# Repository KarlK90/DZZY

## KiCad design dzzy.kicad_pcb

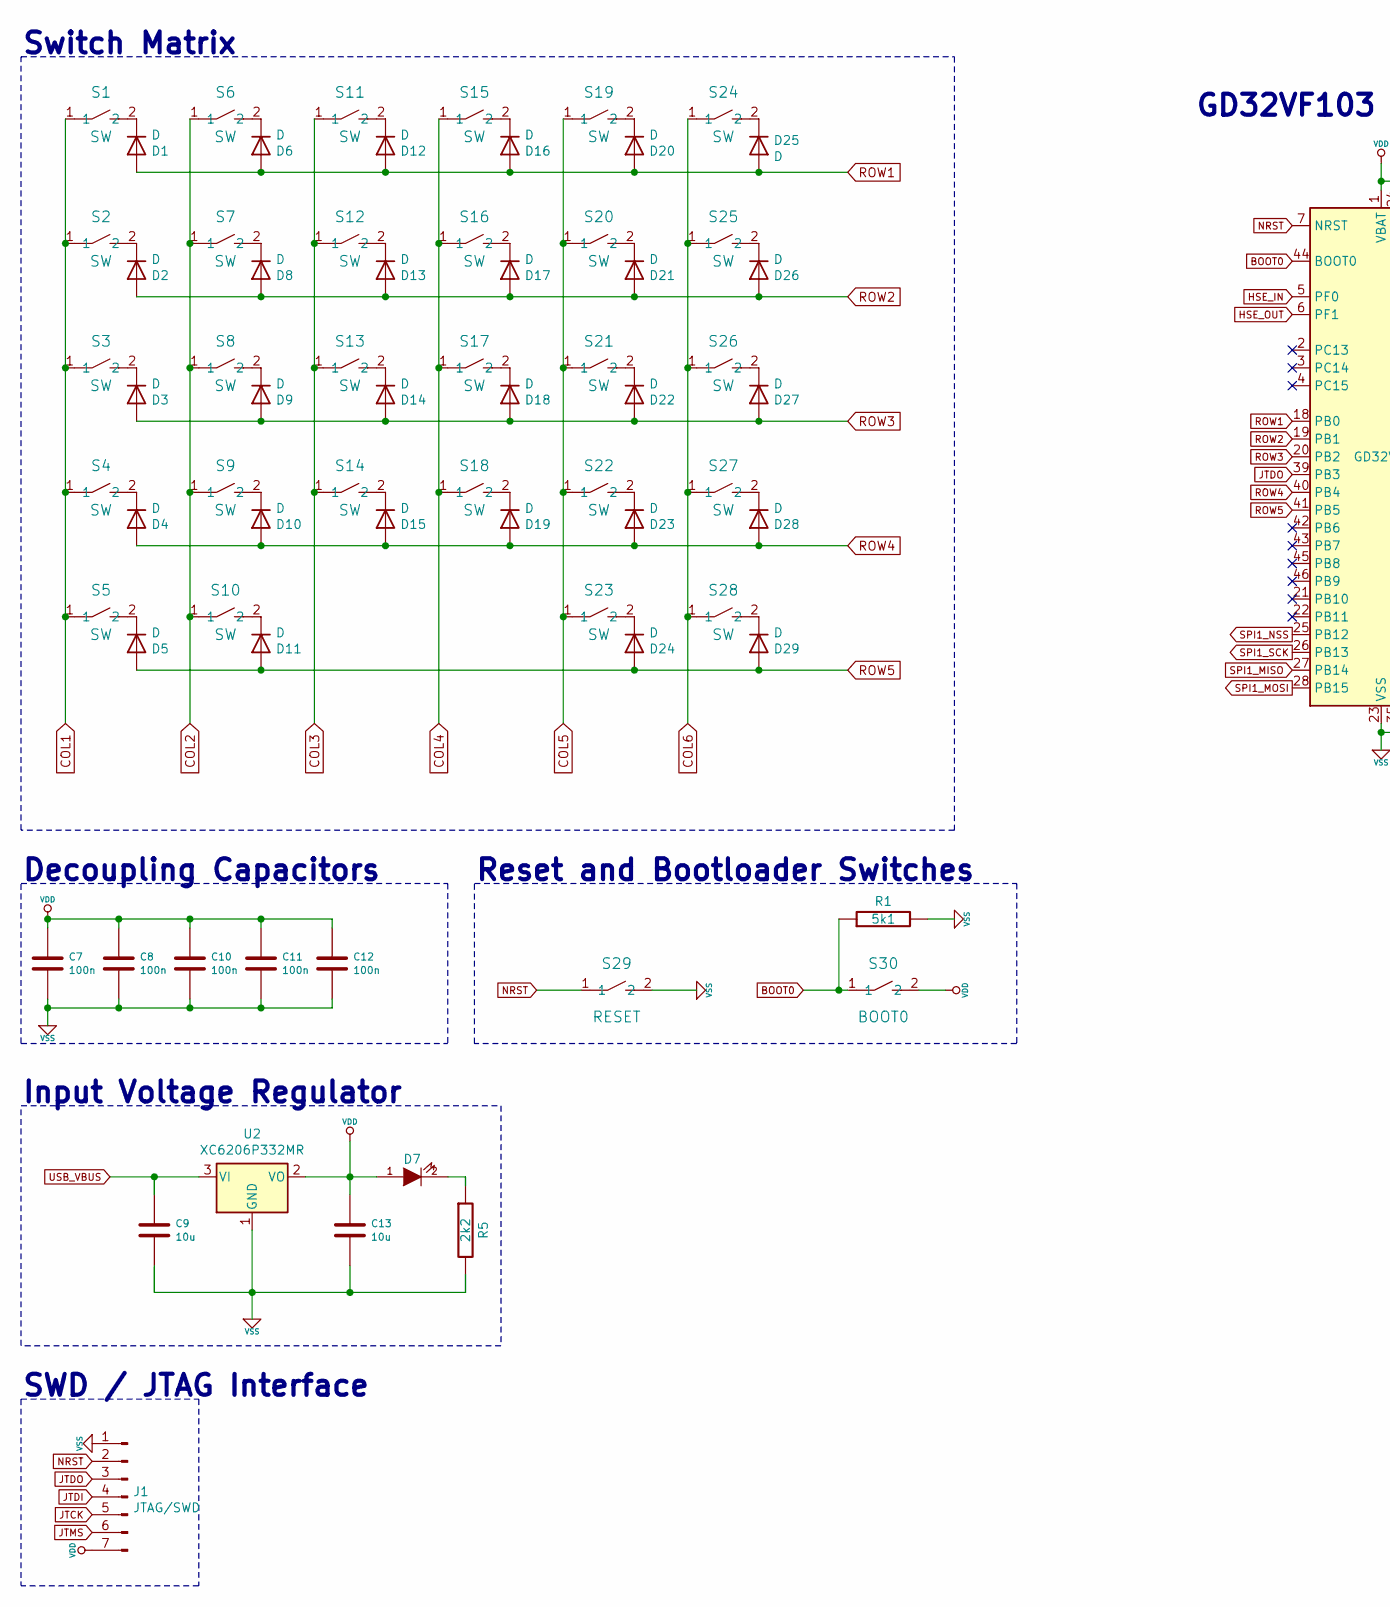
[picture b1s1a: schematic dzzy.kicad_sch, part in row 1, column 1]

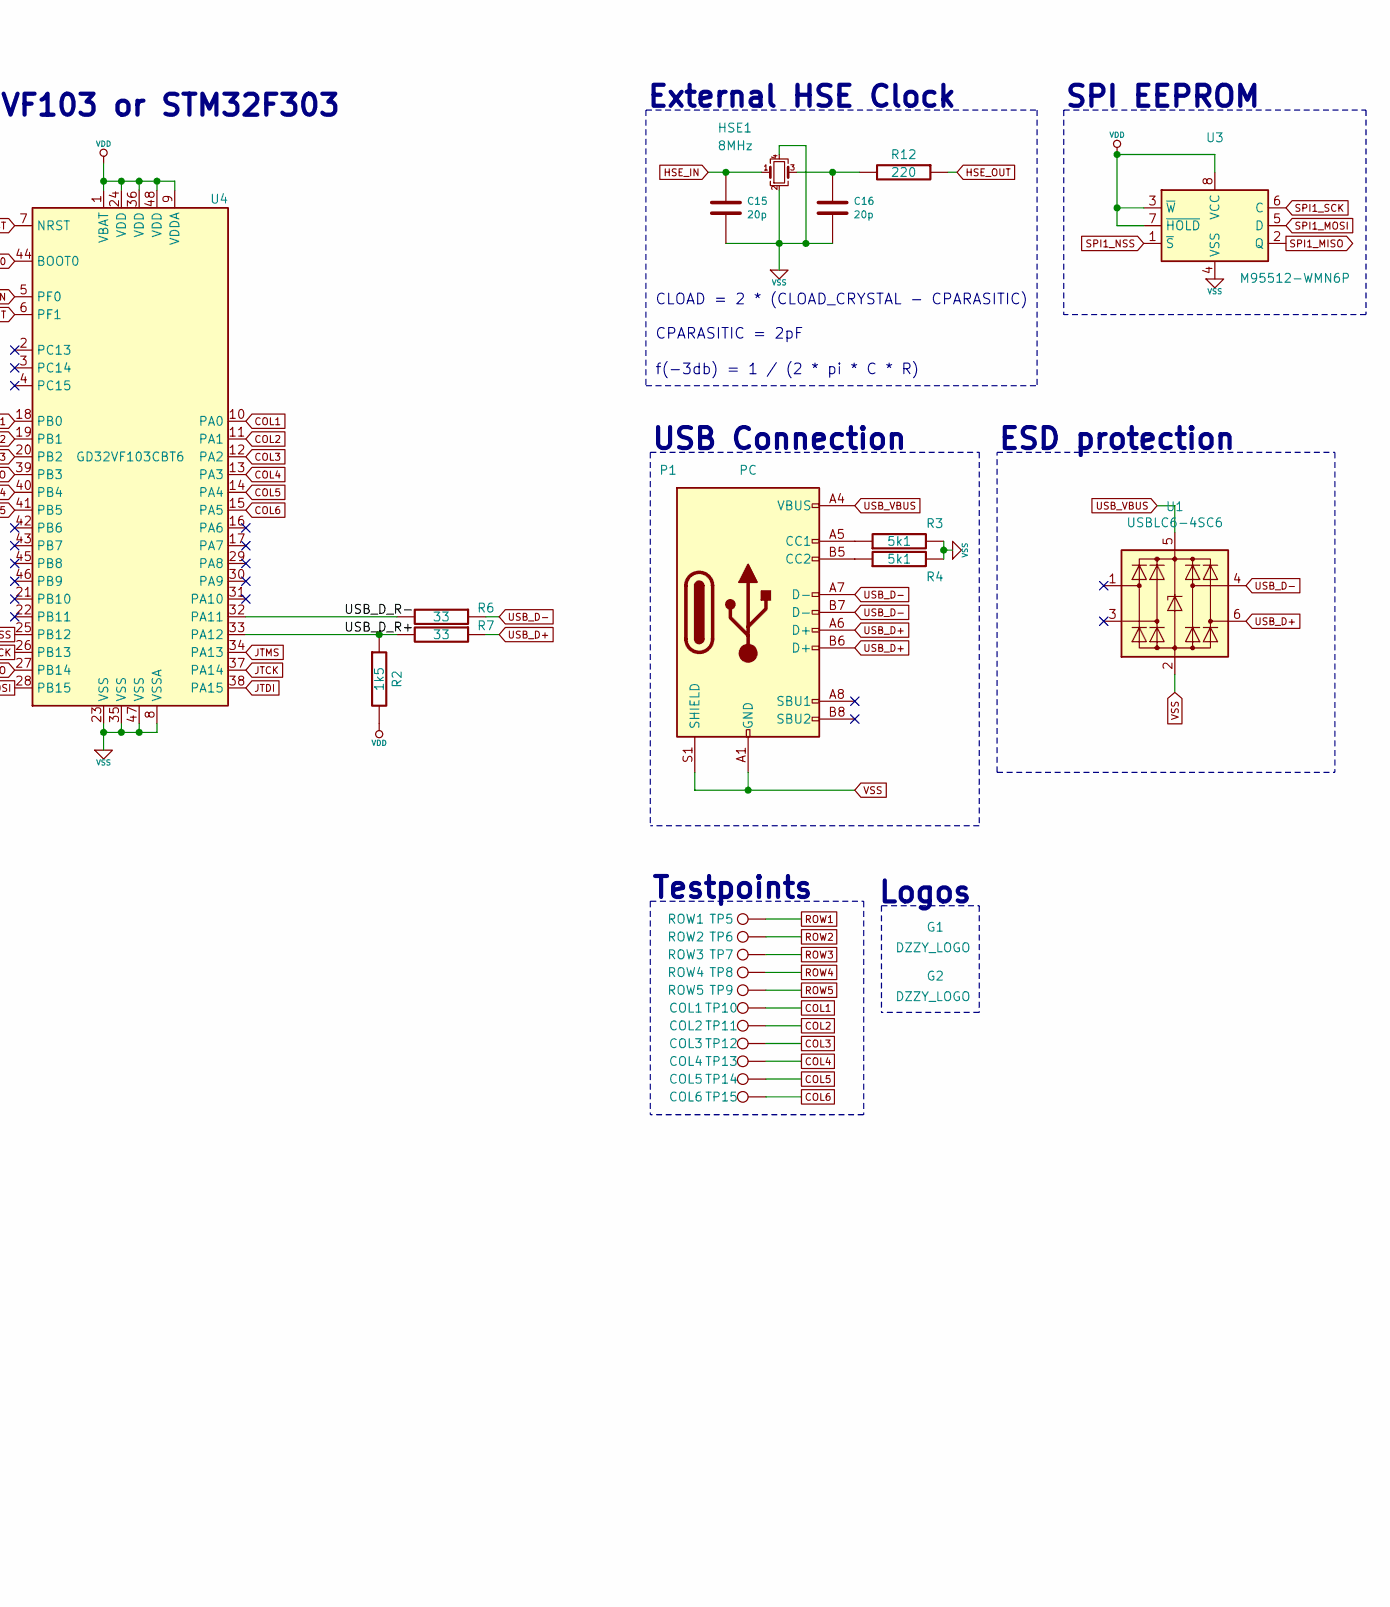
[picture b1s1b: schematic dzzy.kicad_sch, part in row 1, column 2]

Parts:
C7, C8, C10, C11, C12: 100n; SMD-0603; LCSC Part C14663
C9, C13: 10u; SMD-0603; LCSC Part C19702
C15, C16: 20p; SMD-0603; LCSC Part C1648
D1, D2, D3, D4, D5, D6, D8, D9, D10, D11, D12, D13, D14, D15, D16, D17, D18, D19, D20, D21, D22, D23, D24, D25, D26, D27, D28, D29: D; D_SOD-123; LCSC Part C81598
D7: LED; LED-0603_flipable; LCSC Part C72041
G1, G2: DZZY_LOGO; dzzy_logo
HSE1: 8MHz; Crystal_SMD_3225-4Pin_3.2x2.5mm; LCSC Part C403948
J1: JTAG/SWD; Debug_Header_1x07_P2.54mm_Vertical
P1: PC; HRO-TYPE-C-31-M-12-HandSoldering-NoSBU; LCSC Part C168688
R1, R3, R4: 5k1; SMD-0603; LCSC Part C23186
R2: 1k5; SMD-0603; LCSC Part C22843
R5: 2k2; SMD-0603; LCSC Part C4190
R6, R7: 33; SMD-0603; LCSC Part C23140
R12: 220; SMD-0603; LCSC Part C22962
S1, S2, S3, S4, S5, S6, S7, S8, S9, S10, S15, S16, S17, S18, S19, S20, S21, S22, S23, S24, S25, S26, S27, S28: SW; SW_PG1350_reversible; JLCPCB BOM 0
S11, S12, S13, S14: SW; SW_PG1350_0.5u_stagger_reversible; JLCPCB BOM 0
S29: RESET; SW_SPST_TS_1088; LCSC Part C720478
S30: BOOT0; SW_SPST_TS_1088; LCSC Part C720478
TP5: ROW1; TestPoint
TP6: ROW2; TestPoint
TP7: ROW3; TestPoint
TP8: ROW4; TestPoint
TP9: ROW5; TestPoint
TP10: COL1; TestPoint
TP11: COL2; TestPoint
TP12: COL3; TestPoint
TP13: COL4; TestPoint
TP14: COL5; TestPoint
TP15: COL6; TestPoint
U1: USBLC6-4SC6; SOT-23-6_flipable
U2: XC6206P332MR; SOT-23; LCSC Part C5446
U3: M95512-WMN6P; SOIC-8; LCSC Part C7567
U4: GD32VF103CBT6; LQFP-48_7x7mm_P0.5mm; LCSC Part C81523

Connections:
/USB_D_R+: R2.1, R7.2, U4.33 (PA12)
/USB_D_R-: R6.2, U4.32 (PA11)
BOOT0: R1.1, S30.1, U4.44 (BOOT0)
COL1: S1.1, S2.1, S3.1, S4.1, S5.1, TP10.1, U4.10 (PA0)
COL2: S6.1, S7.1, S8.1, S9.1, S10.1, TP11.1, U4.11 (PA1)
COL3: S11.1, S12.1, S13.1, S14.1, TP12.1, U4.12 (PA2)
COL4: S15.1, S16.1, S17.1, S18.1, TP13.1, U4.13 (PA3)
COL5: S19.1, S20.1, S21.1, S22.1, S23.1, TP14.1, U4.14 (PA4)
COL6: S24.1, S25.1, S26.1, S27.1, S28.1, TP15.1, U4.15 (PA5)
HSE_IN: C15.1, HSE1.1, U4.5 (PF0)
HSE_OUT: R12.1, U4.6 (PF1)
JTCK: J1.5, U4.37 (PA14)
JTDI: J1.4, U4.38 (PA15)
JTDO: J1.3, U4.39 (PB3)
JTMS: J1.6, U4.34 (PA13)
NRST: J1.2, S29.1, U4.7 (NRST)
unnamed: C16.1, HSE1.3, R12.2
unnamed: D1.1 (K), S1.2
unnamed: D2.1 (K), S2.2
unnamed: D3.1 (K), S3.2
unnamed: D4.1 (K), S4.2
unnamed: D5.1 (K), S5.2
unnamed: D6.1 (K), S6.2
unnamed: D7.2 (K), R5.1
unnamed: D8.1 (K), S7.2
unnamed: D9.1 (K), S8.2
unnamed: D10.1 (K), S9.2
unnamed: D11.1 (K), S10.2
unnamed: D12.1 (K), S11.2
unnamed: D13.1 (K), S12.2
unnamed: D14.1 (K), S13.2
unnamed: D15.1 (K), S14.2
unnamed: D16.1 (K), S15.2
unnamed: D17.1 (K), S16.2
unnamed: D18.1 (K), S17.2
unnamed: D19.1 (K), S18.2
unnamed: D20.1 (K), S19.2
unnamed: D21.1 (K), S20.2
unnamed: D22.1 (K), S21.2
unnamed: D23.1 (K), S22.2
unnamed: D24.1 (K), S23.2
unnamed: D25.1 (K), S24.2
unnamed: D26.1 (K), S25.2
unnamed: D27.1 (K), S26.2
unnamed: D28.1 (K), S27.2
unnamed: D29.1 (K), S28.2
unnamed: P1.A5 (CC1), R3.1
unnamed: P1.B5 (CC2), R4.1
ROW1: D1.2 (A), D6.2 (A), D12.2 (A), D16.2 (A), D20.2 (A), D25.2 (A), TP5.1, U4.18 (PB0)
ROW2: D2.2 (A), D8.2 (A), D13.2 (A), D17.2 (A), D21.2 (A), D26.2 (A), TP6.1, U4.19 (PB1)
ROW3: D3.2 (A), D9.2 (A), D14.2 (A), D18.2 (A), D22.2 (A), D27.2 (A), TP7.1, U4.20 (PB2)
ROW4: D4.2 (A), D10.2 (A), D15.2 (A), D19.2 (A), D23.2 (A), D28.2 (A), TP8.1, U4.40 (PB4)
ROW5: D5.2 (A), D11.2 (A), D24.2 (A), D29.2 (A), TP9.1, U4.41 (PB5)
SPI1_MISO: U3.2 (Q), U4.27 (PB14)
SPI1_MOSI: U3.5 (D), U4.28 (PB15)
SPI1_NSS: U3.1 (~S), U4.25 (PB12)
SPI1_SCK: U3.6 (C), U4.26 (PB13)
USB_D+: P1.A6 (D+), P1.B6 (D+), R7.1, U1.6 (I/O4)
USB_D-: P1.A7 (D-), P1.B7 (D-), R6.1, U1.4 (I/O3)
USB_VBUS: C9.1, P1.A4 (VBUS), P1.A9 (VBUS), P1.B4 (VBUS), P1.B9 (VBUS), U1.5 (VBUS), U2.3 (VI)
VDD: C7.1, C8.1, C10.1, C11.1, C12.1, C13.1, D7.1 (A), J1.7, R2.2, S30.2, U2.2 (VO), U3.3 (~W), U3.7 (~HOLD), U3.8 (VCC), U4.1 (VBAT), U4.9 (VDDA), U4.24 (VDD), U4.36 (VDD), U4.48 (VDD)
VSS: C7.2, C8.2, C9.2, C10.2, C11.2, C12.2, C13.2, C15.2, C16.2, HSE1.2, HSE1.4, J1.1, P1.A1 (GND), P1.A12 (GND), P1.B1 (GND), P1.B12 (GND), P1.S1 (SHIELD), R1.2, R3.2, R4.2, R5.2, S29.2, U1.2 (GND), U2.1 (GND), U3.4 (VSS), U4.8 (VSSA), U4.23 (VSS), U4.35 (VSS), U4.47 (VSS)

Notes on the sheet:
Switch Matrix
Decoupling Capacitors
Input Voltage Regulator
SWD / JTAG Interface
Reset and Bootloader Switches
GD32VF103 or STM32F303
External HSE Clock
USB Connection
Testpoints
CLOAD = 2 * (CLOAD_CRYSTAL - CPARASITIC) CPARASITIC = 2pF
f(-3db) = 1 / (2 * pi * C * R)
Logos
ESD protection
SPI EEPROM

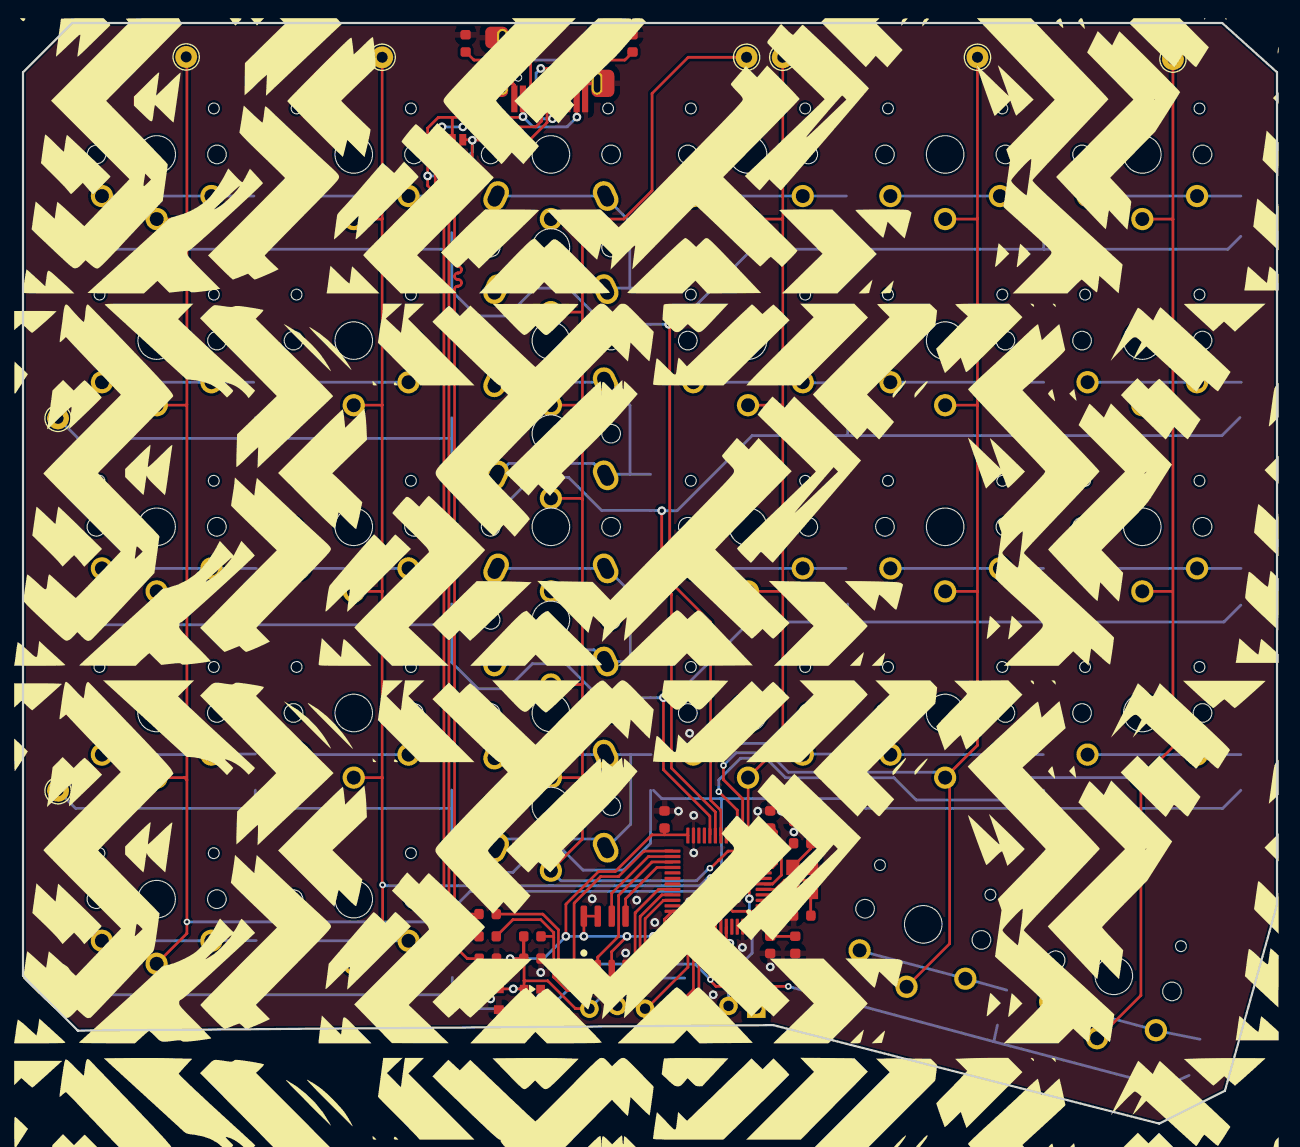
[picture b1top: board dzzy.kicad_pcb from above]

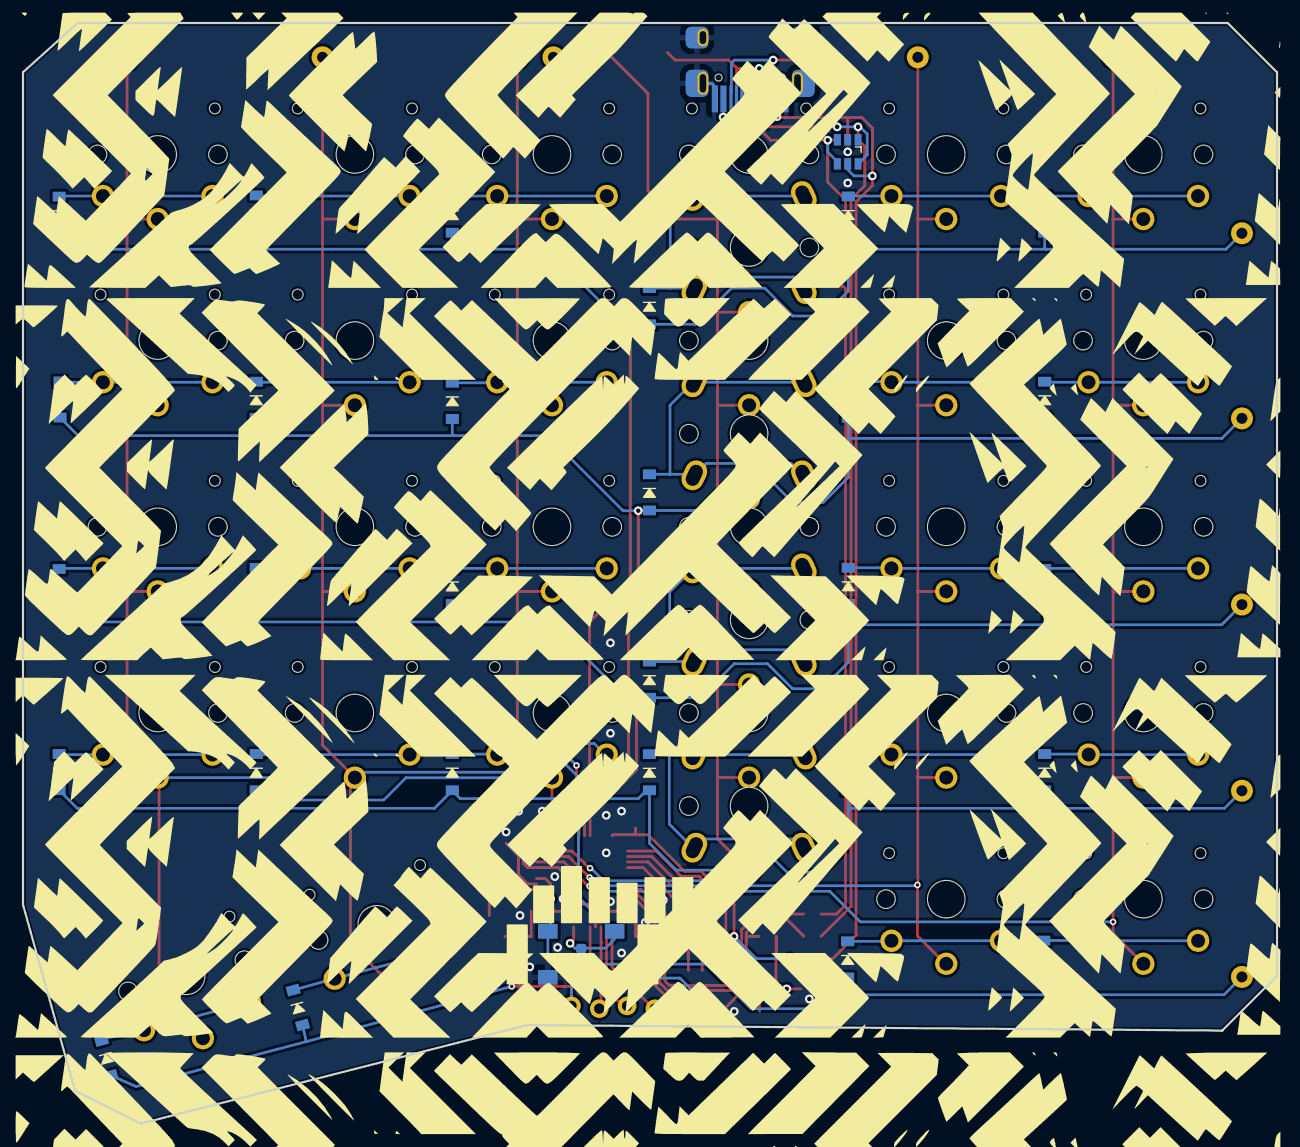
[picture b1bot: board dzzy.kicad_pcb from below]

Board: 2 copper layers, 114.5 x 100.5 mm, 96 parts (32 on the bottom side), 62 nets.

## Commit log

2021-05-21 Add DZZY Rev.1
2021-05-21 Set theme jekyll-theme-cayman
2021-05-22 Update ESD diode placement and silkscreen
